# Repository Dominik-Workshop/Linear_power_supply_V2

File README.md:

# DW3005T - Linear power supply 2

This is the second iteration of my linear power supply project [available on GitHub](https://github.com/Dominik-Workshop/Linear_power_supply), building upon the foundation of my original design. While the first version served as an excellent learning experience, the DW3005T aims to improve upon its predecessor with enhanced performance, better stability, and a more professional design.

## Used tools:
 &nbsp;&nbsp;&nbsp;&nbsp; &nbsp;&nbsp;&nbsp;&nbsp; 

### Project Goals:
- **30V 5A output**
- **Very small output resistance**
- **Precise voltage, current and power measurements**
- **Small output noise**
- **Digital controll** - rotary encoder

## Electronics
### PCBs:
- Power board

<div align="center">
  
</div>

&nbsp;

- Control board
> [!WARNING]  
> WORK IN PROGRESS

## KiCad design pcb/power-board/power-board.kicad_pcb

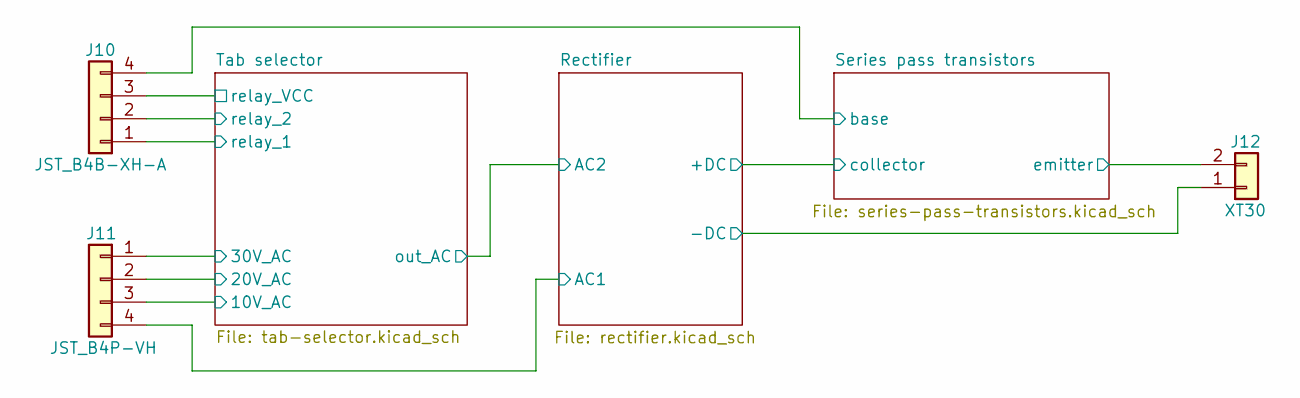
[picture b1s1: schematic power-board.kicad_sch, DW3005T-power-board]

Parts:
J10: JST_B4B-XH-A; JST_XH_B4B-XH-A_1x04_P2.50mm_Vertical
J11: JST_B4P-VH; JST_VH_B4P-VH_1x04_P3.96mm_Vertical
J12: XT30; AMASS_XT30U-F_1x02_P5.0mm_Vertical

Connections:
/Rectifier/-DC: J12.1; also elsewhere on the board
/Rectifier/AC1: J11.4; also elsewhere on the board
/Series pass transistors/base: J10.4; also elsewhere on the board
/Series pass transistors/emitter: J12.2; also elsewhere on the board
/Tab selector/10V_AC: J11.3; also elsewhere on the board
/Tab selector/20V_AC: J11.2; also elsewhere on the board
/Tab selector/30V_AC: J11.1; also elsewhere on the board
/Tab selector/relay_1: J10.1; also elsewhere on the board
/Tab selector/relay_2: J10.2; also elsewhere on the board
/Tab selector/relay_VCC: J10.3; also elsewhere on the board

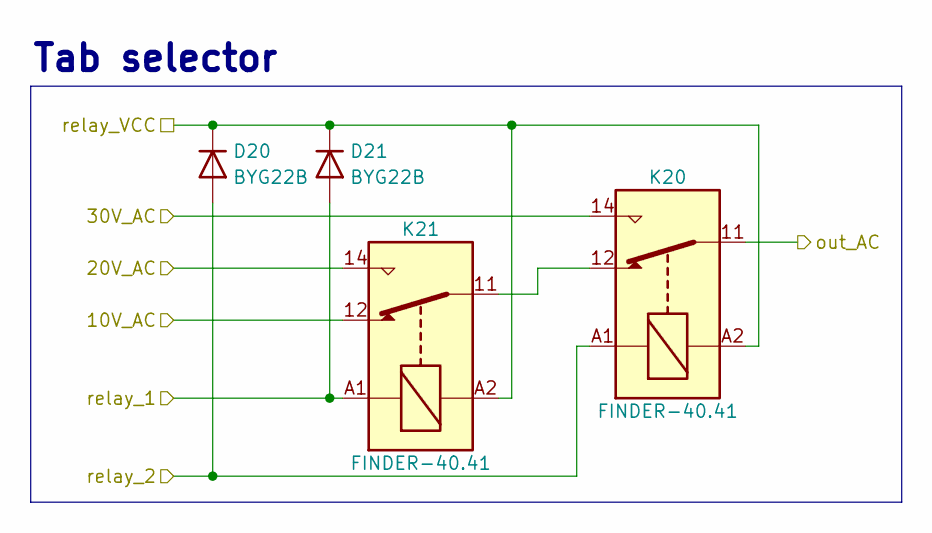
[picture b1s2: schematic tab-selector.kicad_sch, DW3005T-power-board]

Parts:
D20, D21: BYG22B; D_SMA; MPN BYG22B-E3/TR
K20, K21: FINDER-40.41; Relay_SPDT_Finder_36.11

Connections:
/Rectifier/AC2: K20.11; also elsewhere on the board
/Tab selector/10V_AC: K21.12; also elsewhere on the board
/Tab selector/20V_AC: K21.14; also elsewhere on the board
/Tab selector/30V_AC: K20.14; also elsewhere on the board
/Tab selector/relay_1: D21.2 (A), K21.A1; also elsewhere on the board
/Tab selector/relay_2: D20.2 (A), K20.A1; also elsewhere on the board
/Tab selector/relay_VCC: D20.1 (K), D21.1 (K), K20.A2, K21.A2; also elsewhere on the board
unnamed: K20.12, K21.11

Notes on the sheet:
Tab selector

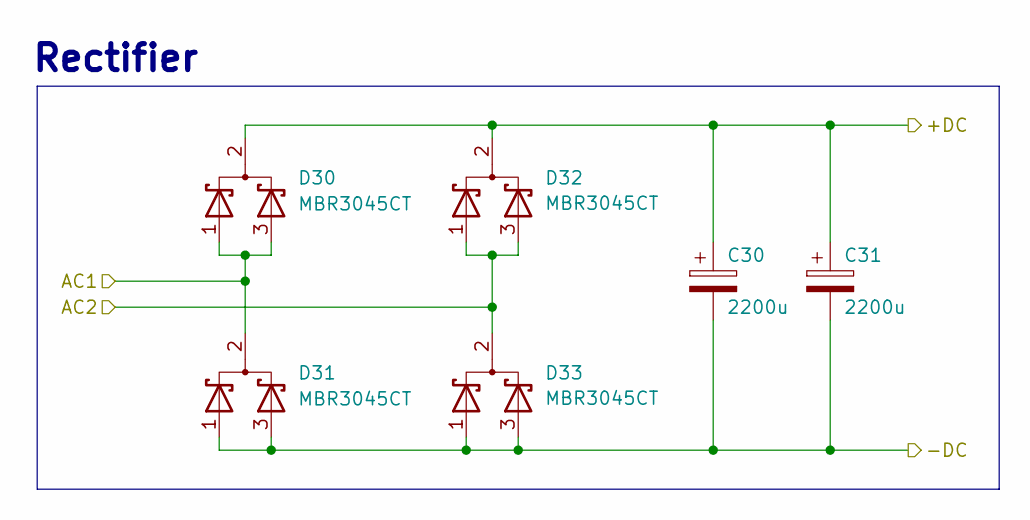
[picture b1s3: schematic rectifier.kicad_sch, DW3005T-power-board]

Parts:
C30, C31: 2200u; CP_Radial_D22.0mm_P10.00mm_SnapIn
D30, D31, D32, D33: MBR3045CT; TO-220-3_Horizontal_TabUp

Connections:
/Rectifier/+DC: C30.1, C31.1, D30.2 (A), D32.2 (A); also elsewhere on the board
/Rectifier/-DC: C30.2, C31.2, D31.1 (K), D31.3 (K), D33.1 (K), D33.3 (K); also elsewhere on the board
/Rectifier/AC1: D30.1 (K), D30.3 (K), D31.2 (A); also elsewhere on the board
/Rectifier/AC2: D32.1 (K), D32.3 (K), D33.2 (A); also elsewhere on the board

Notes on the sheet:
Rectifier

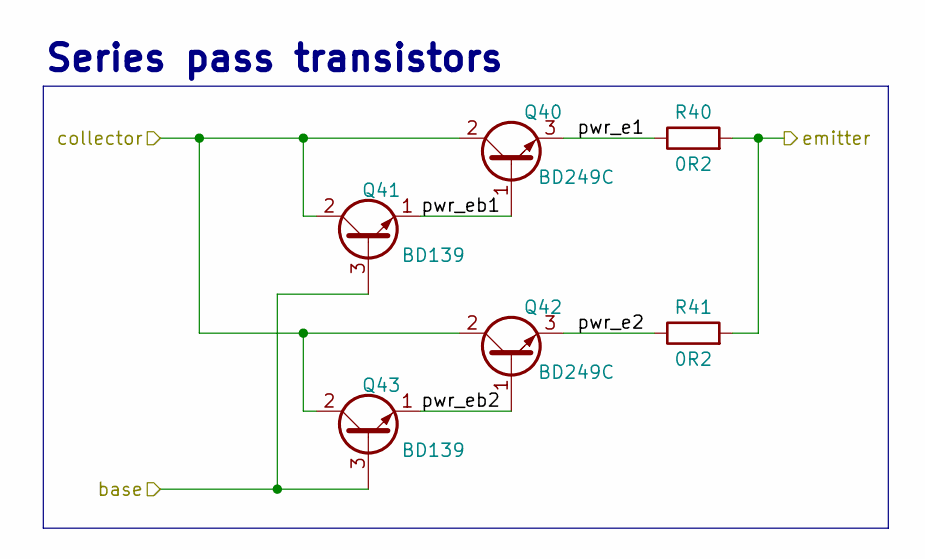
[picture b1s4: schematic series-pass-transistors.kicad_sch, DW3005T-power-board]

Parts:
Q40, Q42: BD249C; TO-247-3_Horizontal_TabUp
Q41, Q43: BD139; TO-126-3_Horizontal_TabUp
R40, R41: 0R2; R_Axial_DIN0414_L11.9mm_D4.5mm_P15.24mm_Horizontal

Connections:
/Rectifier/+DC: Q40.2 (C), Q41.2 (C), Q42.2 (C), Q43.2 (C); also elsewhere on the board
/Series pass transistors/base: Q41.3 (B), Q43.3 (B); also elsewhere on the board
/Series pass transistors/emitter: R40.2, R41.2; also elsewhere on the board
/Series pass transistors/pwr_e1: Q40.3 (E), R40.1
/Series pass transistors/pwr_e2: Q42.3 (E), R41.1
/Series pass transistors/pwr_eb1: Q40.1 (B), Q41.1 (E)
/Series pass transistors/pwr_eb2: Q42.1 (B), Q43.1 (E)

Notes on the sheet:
Series pass transistors

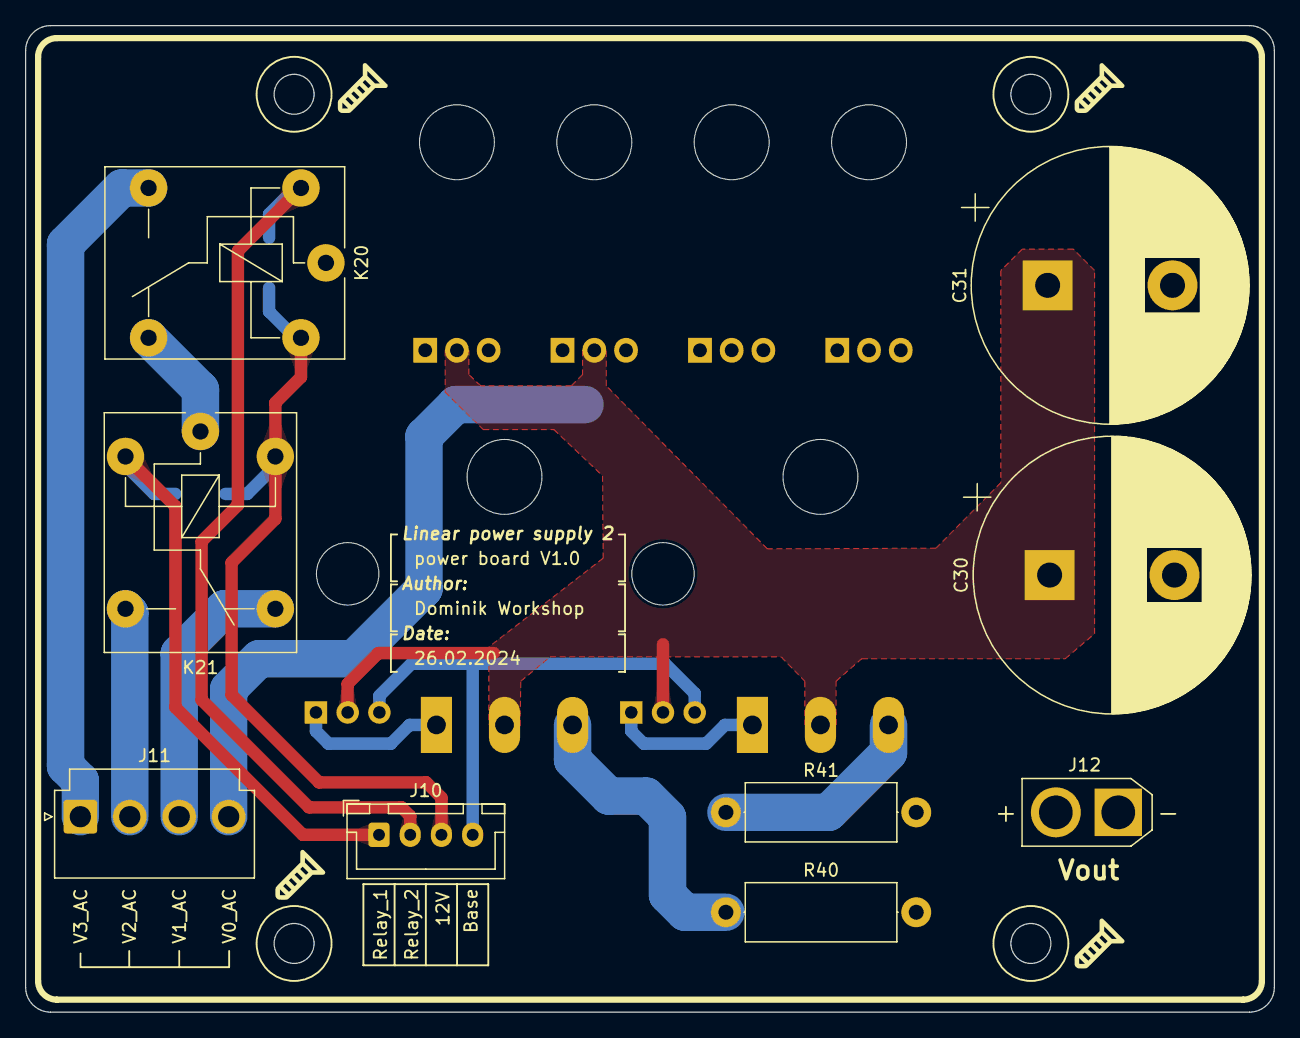
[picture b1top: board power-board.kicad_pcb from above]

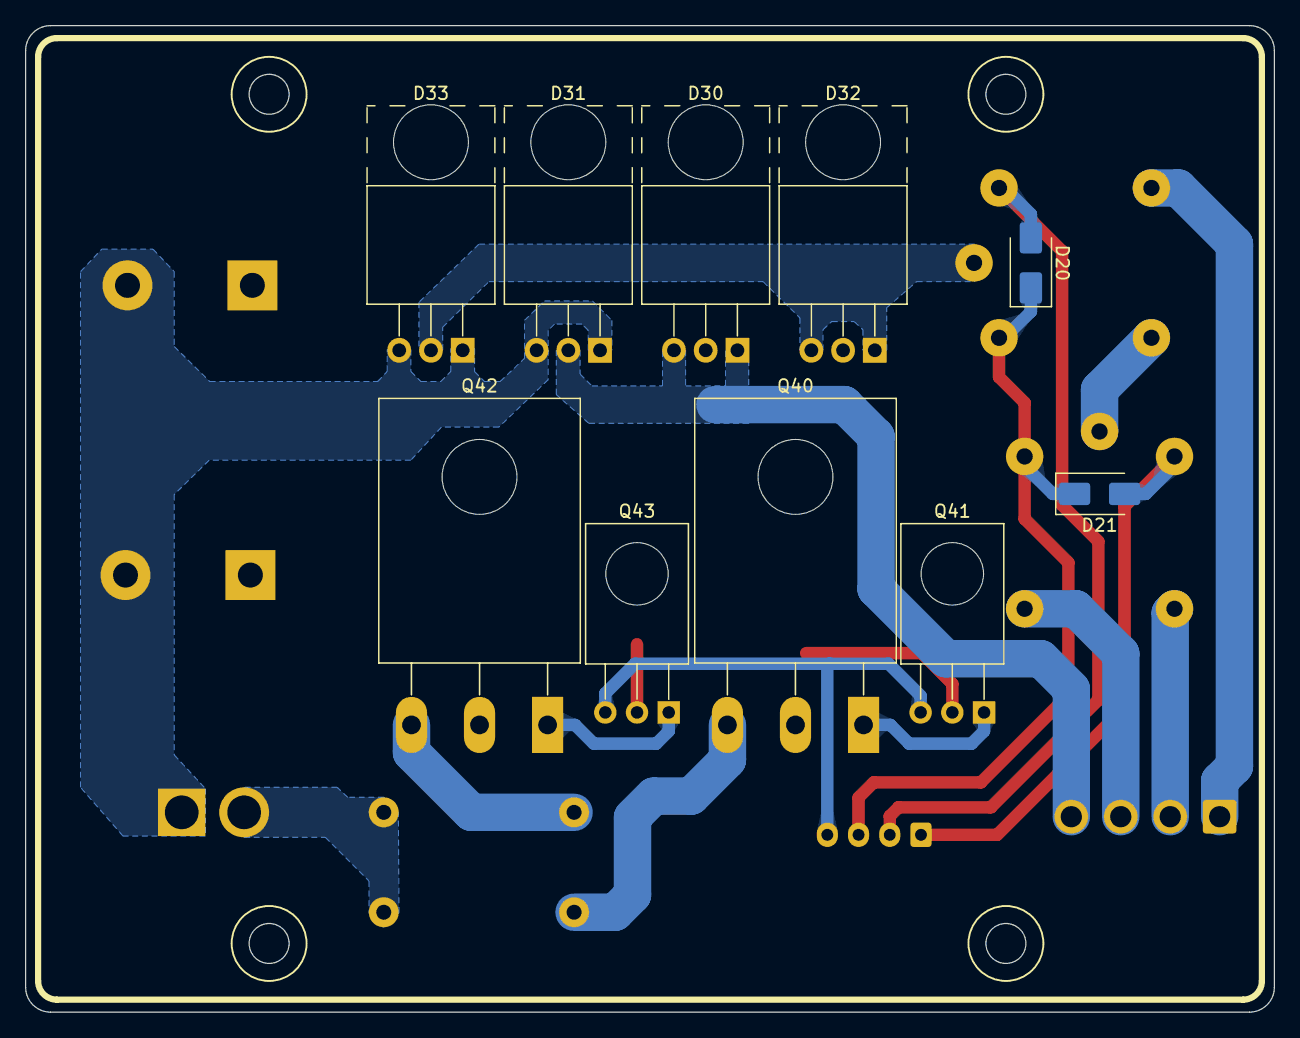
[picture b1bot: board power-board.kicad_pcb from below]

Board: 2 copper layers, 100.0 x 79.0 mm, 19 parts (10 on the bottom side), 17 nets.

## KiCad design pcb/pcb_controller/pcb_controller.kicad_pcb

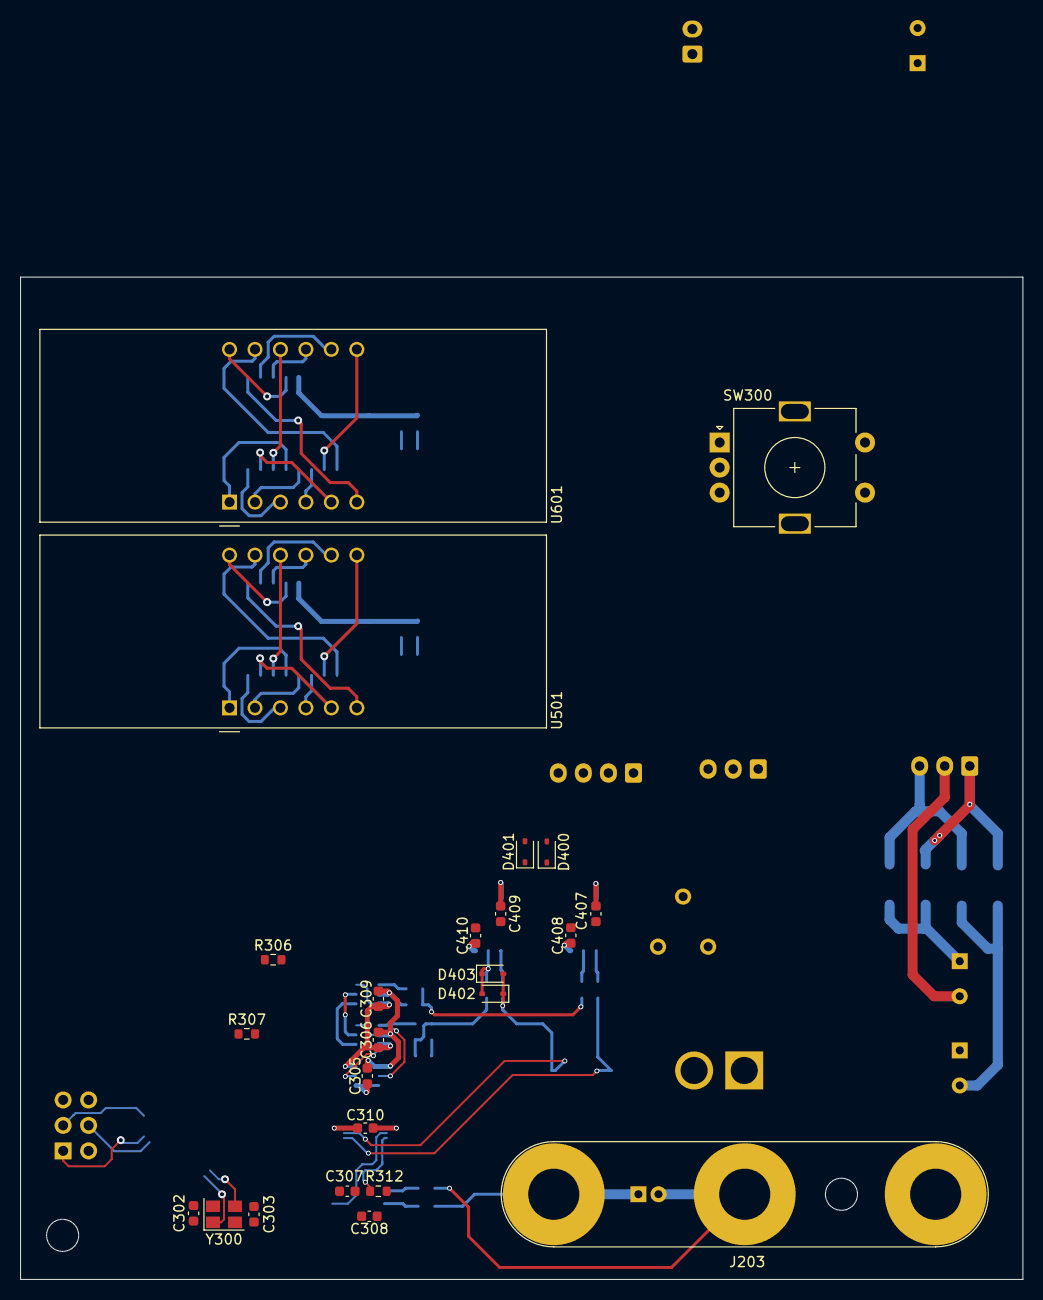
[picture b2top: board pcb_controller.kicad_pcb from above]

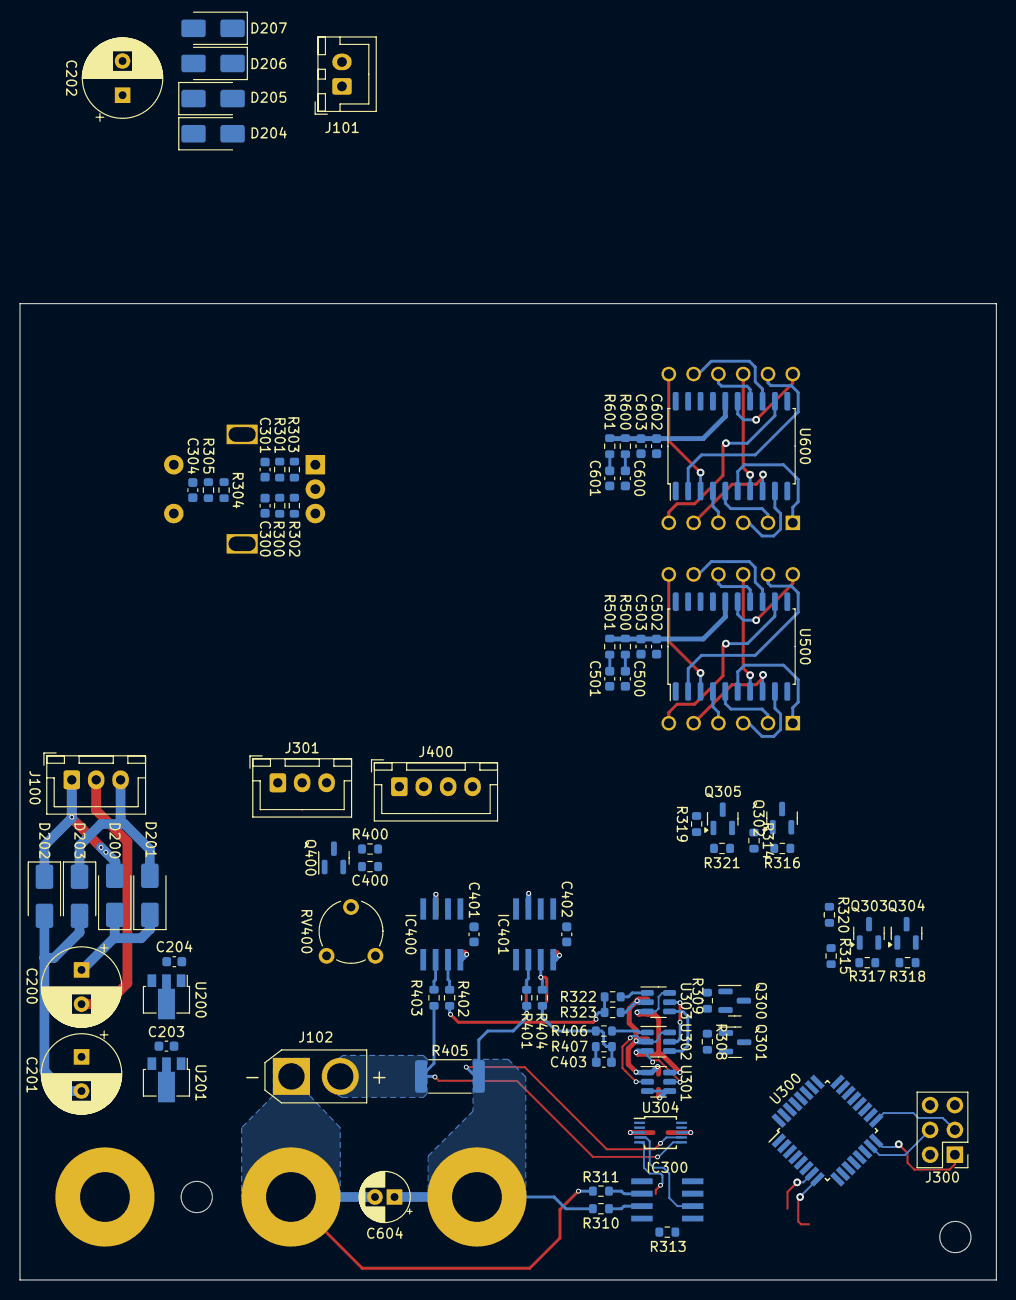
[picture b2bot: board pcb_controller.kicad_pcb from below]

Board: 2 copper layers, 100.0 x 100.0 mm, 112 parts (88 on the bottom side), 81 nets.

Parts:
C200, C201, C202: 1000u; CP_Radial_D8.0mm_P3.50mm
C203, C204, C300, C301, C304, C306, C307, C308, C309, C310, C407, C408, C409, C410, C502, C602: 100n; C_0603_1608Metric
C302, C303: 20p; C_0603_1608Metric
C305: 470n; C_0603_1608Metric
C400: 10u; R_0603_1608Metric
C401, C402: 22p; C_0603_1608Metric
C403: 1n; C_0603_1608Metric
C500, C501, C600, C601: 100p; C_0603_1608Metric
C503, C603: 10u; C_0603_1608Metric
C604: 10u; CP_Radial_D5.0mm_P2.00mm
D200, D201, D202, D203, D204, D205, D206, D207: B360; D_SMA
D400, D401, D402, D403: 1N4148WS; D_SOD-323
IC300, IC400, IC401: OPA277; SO08
J100, J301: JST_XH_B3B-XH; JST_XH_B3B-XH-A_1x03_P2.50mm_Vertical
J101: JST_XH_B2B-XH; JST_XH_B2B-XH-A_1x02_P2.50mm_Vertical
J102: XT30; AMASS_XT30U-M_1x02_P5.0mm_Vertical
J203: Banana conn; Banana_Jack_3Pin
J300: Goldpin_2x3; PinHeader_2x03_P2.54mm_Vertical
J400: JST_XH_B4B-XH; JST_XH_B4B-XH-A_1x04_P2.50mm_Vertical
Q300, Q301, Q303: 2N7002; SOT-23
Q302, Q305: CJ2306; SOT-23
Q304: BSS83P; SOT-23
Q400: S9015; SOT-23
R300, R301, R302, R303, R304, R305, R306, R307, R308, R309, R322, R323, R404: 4k7; R_0603_1608Metric
R310, R311: 100k; R_0603_1608Metric
R312, R313, R316, R317, R318, R320, R321, R401, R402, R500, R501, R600, R601: 10k; R_0603_1608Metric
R314, R315, R319, R400: 220R; R_0603_1608Metric
R403: 22k; R_0603_1608Metric
R405: 15m; R_2512_6332Metric
R406: 10k?; R_0603_1608Metric
R407: 100k?; R_0603_1608Metric
RV400: 4k7; Potentiometer_Piher_PT-6-V_Vertical
SW300: RotaryEncoder_Switch; RotaryEncoder_Alps_EC11E-Switch_Vertical_H20mm
U200: MC78L05; SOT-89-3
U201: MC79L05; SOT-89-3
U300: ATmega328P-A; TQFP-32_7x7mm_P0.8mm
U301: REF3240; SOT-23-6
U302, U303: MCP4725; SOT-23-6
U304: ADS1115IDGS; TSSOP-10_3x3mm_P0.5mm
U500, U600: TM1637; SOP-20_7.5x12.8mm_P1.27mm
U501, U601: CL5641BH; CA56-12SURKWA
Y300: 16MHz; Crystal_SMD_SeikoEpson_TSX3225-4Pin_3.2x2.5mm

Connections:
+4V: C306.2, C309.2, Q300.1 (G), Q301.1 (G), R308.1, R309.1, U301.5 (OUT_S), U301.6 (OUT_F), U302.3 (VDD), U303.3 (VDD), U303.6 (A0)
+5V: C204.2, C305.2, C307.2, C310.2, C400.1, C407.2, C409.1, C502.1, C503.1, C602.1, C603.1, IC300.7, IC400.7, IC401.7, J300.2, R302.2, R303.2, R304.2, R306.1, R307.1, R320.1, R400.2, R500.1, R501.1, R600.1, R601.1, RV400.1, U200.1 (OUT), U300.4 (VCC), U300.6 (VCC), U300.18 (AVCC), U301.3 (ENABLE), U301.4 (VIN), U304.8 (VDD), U500.16 (VDD), U600.16 (VDD)
+12V: C202.1, D204.1 (K), D205.1 (K), J400.3, Q304.2 (S), R318.1
-5V: C203.1, C308.1, C408.2, C410.2, IC300.4, IC400.4, IC401.4, U201.3 (VO)
/Linear regulator/+in_CC_amp: IC400.3, R402.2
/Linear regulator/+in_CV_amp: D402.2 (A), D403.1 (K), IC401.3, R404.2
/Linear regulator/-Vin: C403.1, C604.2, J102.1, J203.2, R311.1, R407.2
/Linear regulator/-in_CC_amp: C401.2, IC400.2, R403.2
/Linear regulator/-in_CV_amp: C402.2, IC401.2, R401.2
/Linear regulator/I_set: R322.2, R323.1, R402.1
/Linear regulator/U_set: R406.1, U302.1 (VOUT)
/Linear regulator/Vout_div: C403.2, R404.1, R406.2, R407.1
/Linear regulator/ccs_b: C400.2, Q400.2 (B), RV400.2
/Linear regulator/ccs_e: Q400.3 (E), R400.1
/Linear regulator/out_CC_amp: C401.1, D400.1 (K), IC400.6
/Linear regulator/out_CV_amp: C402.1, D401.1 (K), IC401.6
/Linear regulator/pwr_base: D400.2 (A), D401.2 (A), J400.4, Q400.1 (C)
/MCU/+in_s_amp: IC300.3, R310.2, R312.1
/MCU/-in_s_amp: IC300.2, R311.2, R313.1
/MCU/I_DAC_out: R322.1, U303.1 (VOUT)
/MCU/I_disp_CLK: C601.1, R601.2, U300.9 (PD5), U600.18 (CLK)
/MCU/I_disp_DIO: C600.1, R600.2, U300.2 (PD4), U600.17 (DIO)
/MCU/MISO: J300.1, U300.16 (PB4)
/MCU/MOSI: J300.4, U300.15 (PB3)
/MCU/RST: J300.5, U300.29 (~RESET/PC6)
/MCU/SCK: J300.3, U300.17 (PB5)
/MCU/SCL: Q300.3 (D), R306.2, U300.28 (PC5), U304.10 (SCL)
/MCU/SCL_4V: Q300.2 (S), R309.2, U302.5 (SCL), U303.5 (SCL)
/MCU/SDA: Q301.3 (D), R307.2, U300.27 (PC4), U304.9 (SDA)
/MCU/SDA_4V: Q301.2 (S), R308.2, U302.4 (SDA), U303.4 (SDA)
/MCU/U_disp_CLK: C501.1, R501.2, U300.11 (PD7), U500.18 (CLK)
/MCU/U_disp_DIO: C500.1, R500.2, U300.10 (PD6), U500.17 (DIO)
/MCU/Vout_meas: IC300.6, R313.2, U304.4 (AIN0)
/MCU/XTAL1: C303.1, U300.7 (XTAL1/PB6), Y300.3
/MCU/XTAL2: C302.1, U300.8 (XTAL2/PB7), Y300.1
/MCU/_e_A: R301.2, R303.1, SW300.A
/MCU/_e_B: R300.2, R302.1, SW300.B
/MCU/_e_bt: R304.1, R305.1, SW300.S1
/MCU/enc_A: C301.1, R301.1
/MCU/enc_B: C300.1, R300.1
/MCU/enc_button: C304.1, R305.2
/MCU/fan_tacho: J301.3, R320.2
/MCU/fan_v+: J301.2, Q304.3 (D)
/MCU/fpwm_g: Q303.3 (D), Q304.1 (G), R318.2
/MCU/fpwm_r: Q303.1 (G), R315.1, R317.1
/MCU/r1g_r: Q302.1 (G), R314.1, R316.1
/MCU/r2g_r: Q305.1 (G), R319.1, R321.1
/MCU/relay1: J400.1, Q302.3 (D)
/MCU/relay2: J400.2, Q305.3 (D)
/Power/12VAC1: D204.2 (A), D206.1 (K), J101.2
/Power/12VAC2: D205.2 (A), D207.1 (K), J101.1
/Power/+7VAC: D201.2 (A), D203.1 (K), J100.3
/Power/+9V_unreg: C200.1, D200.1 (K), D201.1 (K), U200.3 (IN)
/Power/-7VAC: D200.2 (A), D202.1 (K), J100.1
/Power/-9V_unreg: C201.2, D202.2 (A), D203.2 (A), U201.2 (VI)
GND: C200.2, C201.1, C202.2, C203.2, C204.1, C300.2, C301.2, C302.2, C303.2, C304.2, C305.1, C306.1, C307.1, C308.2, C309.1, C310.1, C407.1, C408.1, C409.2, C410.1, C500.2, C501.2, C502.2, C503.2, C600.2, C601.2, C602.2, C603.2, C604.1, D206.2 (A), D207.2 (A), D402.1 (K), D403.2 (A), J100.2, J203.1, J300.6, J301.1, Q302.2 (S), Q303.2 (S), Q305.2 (S), R310.1, R312.2, R316.2, R317.2, R321.2, R323.2, R401.1, R405.2, RV400.3, SW300.C, SW300.S2, U200.2 (GND), U201.1 (GND), U300.3 (GND), U300.5 (GND), U300.21 (GND), U301.1 (GNDF), U301.2 (GNDS), U302.2 (VSS), U302.6 (A0), U303.2 (VSS), U304.1 (ADDR), U304.3 (GND), U304.5 (AIN1), U304.7 (AIN3), U500.1 (GND), U600.1 (GND), Y300.2, Y300.4
I_meas: J102.2, R403.1, R405.1, U304.6 (AIN2)
unnamed: U500.15 (GRID1), U501.12 (CA1)
unnamed: U500.14 (GRID2), U501.9 (CA2)
unnamed: U500.13 (GRID3), U501.8 (CA3)
unnamed: U500.12 (GRID4), U501.6 (CA4)
unnamed: U500.2 (SEG1/KS1), U501.11 (a)
unnamed: U500.3 (SEG2/KS2), U501.7 (b)
unnamed: U500.4 (SEG3/KS3), U501.4 (c)
unnamed: U500.5 (SEG4/KS4), U501.2 (d)
unnamed: U500.6 (SEG5/KS5), U501.1 (e)
unnamed: U500.7 (SEG6/KS6), U501.10 (f)
unnamed: U500.8 (SEG7/KS7), U501.5 (g)
unnamed: U500.9 (SEG8/KS8), U501.3 (DPX)
unnamed: U600.15 (GRID1), U601.12 (CA1)
unnamed: U600.14 (GRID2), U601.9 (CA2)
unnamed: U600.13 (GRID3), U601.8 (CA3)
unnamed: U600.12 (GRID4), U601.6 (CA4)
unnamed: U600.2 (SEG1/KS1), U601.11 (a)
unnamed: U600.3 (SEG2/KS2), U601.7 (b)
unnamed: U600.4 (SEG3/KS3), U601.4 (c)
unnamed: U600.5 (SEG4/KS4), U601.2 (d)
unnamed: U600.6 (SEG5/KS5), U601.1 (e)
unnamed: U600.7 (SEG6/KS6), U601.10 (f)
unnamed: U600.8 (SEG7/KS7), U601.5 (g)
unnamed: U600.9 (SEG8/KS8), U601.3 (DPX)

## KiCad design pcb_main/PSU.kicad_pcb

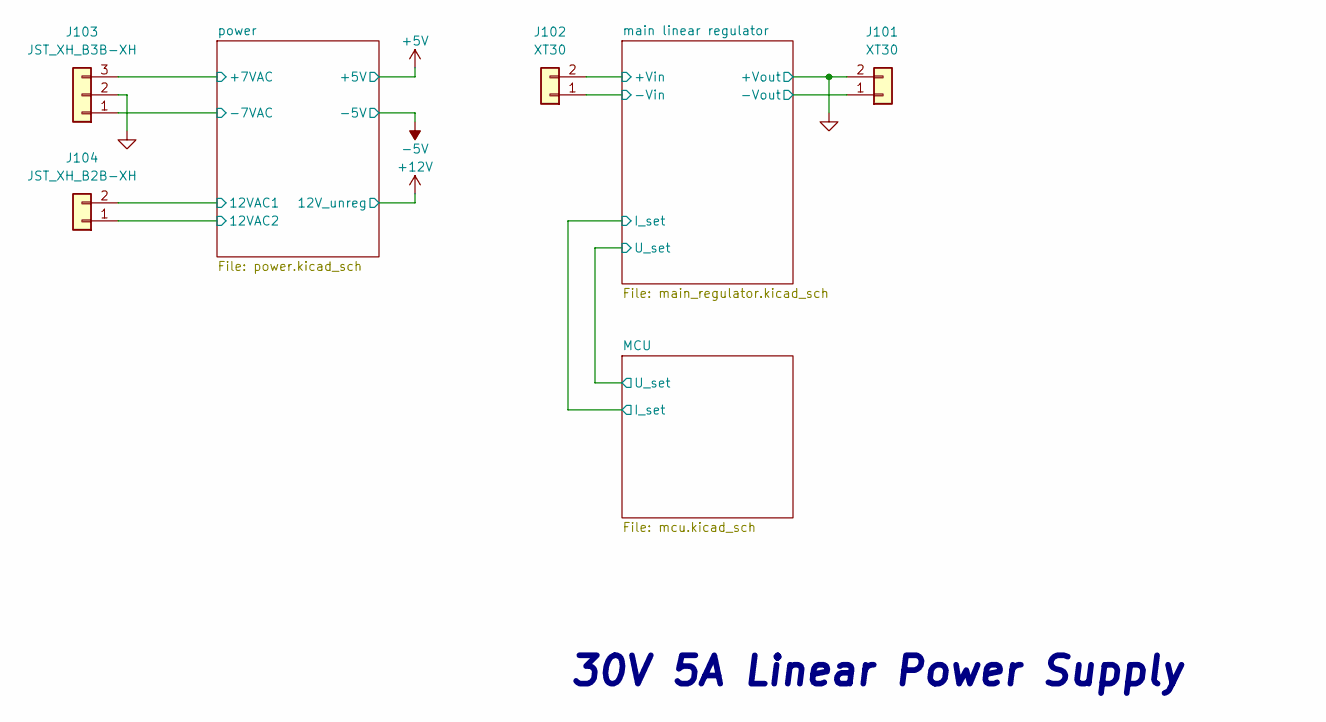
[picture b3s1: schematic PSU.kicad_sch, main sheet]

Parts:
J101, J102: XT30; AMASS_XT30U-M_1x02_P5.0mm_Vertical
J103: JST_XH_B3B-XH; JST_XH_B3B-XH-A_1x03_P2.50mm_Vertical
J104: JST_XH_B2B-XH; JST_XH_B2B-XH-A_1x02_P2.50mm_Vertical

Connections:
/main linear regulator/+Vin: J102.2; also elsewhere on the board
/main linear regulator/-Vin: J101.1, J102.1; also elsewhere on the board
/power/12VAC1: J104.2; also elsewhere on the board
/power/12VAC2: J104.1; also elsewhere on the board
/power/+7VAC: J103.3; also elsewhere on the board
/power/-7VAC: J103.1; also elsewhere on the board
GND: J101.2, J103.2; also elsewhere on the board

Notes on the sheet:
30V 5A Linear Power Supply

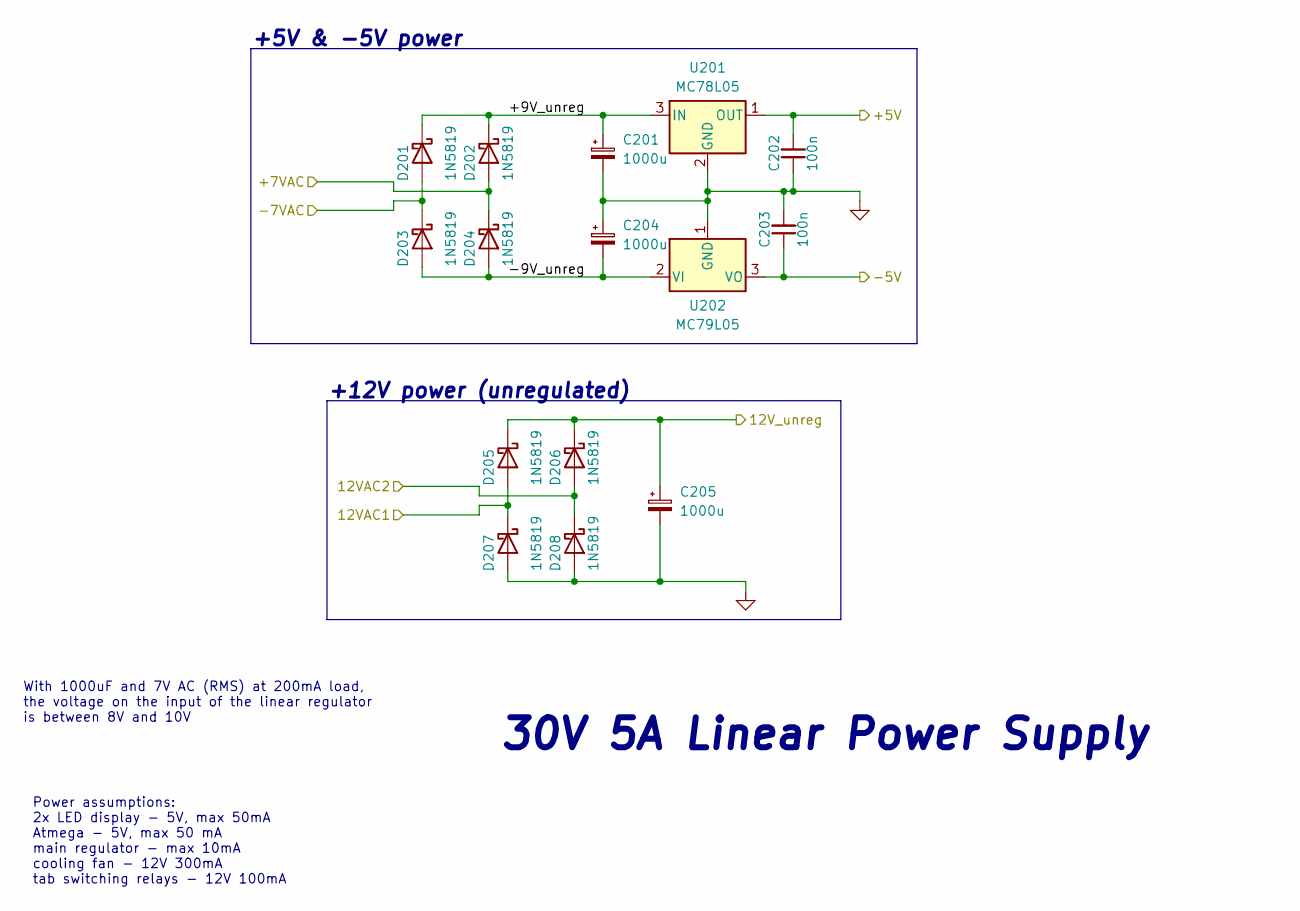
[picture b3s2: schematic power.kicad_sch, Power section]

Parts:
C201, C204, C205: 1000u; CP_Radial_D8.0mm_P3.50mm
C202, C203: 100n; C_0603_1608Metric
D201, D202, D203, D204, D205, D206, D207, D208: 1N5819; D_DO-41_SOD81_P10.16mm_Horizontal
U201: MC78L05; SOT-89-3
U202: MC79L05; SOT-89-3

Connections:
+5V: C202.2, U201.1 (OUT); also elsewhere on the board
+12V: C205.1, D205.1 (K), D206.1 (K)
-5V: C203.1, U202.3 (VO); also elsewhere on the board
/power/12VAC1: D205.2 (A), D207.1 (K); also elsewhere on the board
/power/12VAC2: D206.2 (A), D208.1 (K); also elsewhere on the board
/power/+7VAC: D202.2 (A), D204.1 (K); also elsewhere on the board
/power/+9V_unreg: C201.1, D201.1 (K), D202.1 (K), U201.3 (IN)
/power/-7VAC: D201.2 (A), D203.1 (K); also elsewhere on the board
/power/-9V_unreg: C204.2, D203.2 (A), D204.2 (A), U202.2 (VI)
GND: C201.2, C202.1, C203.2, C204.1, C205.2, D207.2 (A), D208.2 (A), U201.2 (GND), U202.1 (GND); also elsewhere on the board

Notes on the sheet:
30V 5A Linear Power Supply
Power assumptions: 2x LED display - 5V, max 50mA Atmega - 5V, max 50 mA main regulator - max 10mA cooling fan - 12V 300mA tab switching relays - 12V 100mA
+5V & -5V power
+12V power (unregulated)
With 1000uF and 7V AC (RMS) at 200mA load, the voltage on the input of the linear regulator is between 8V and 10V

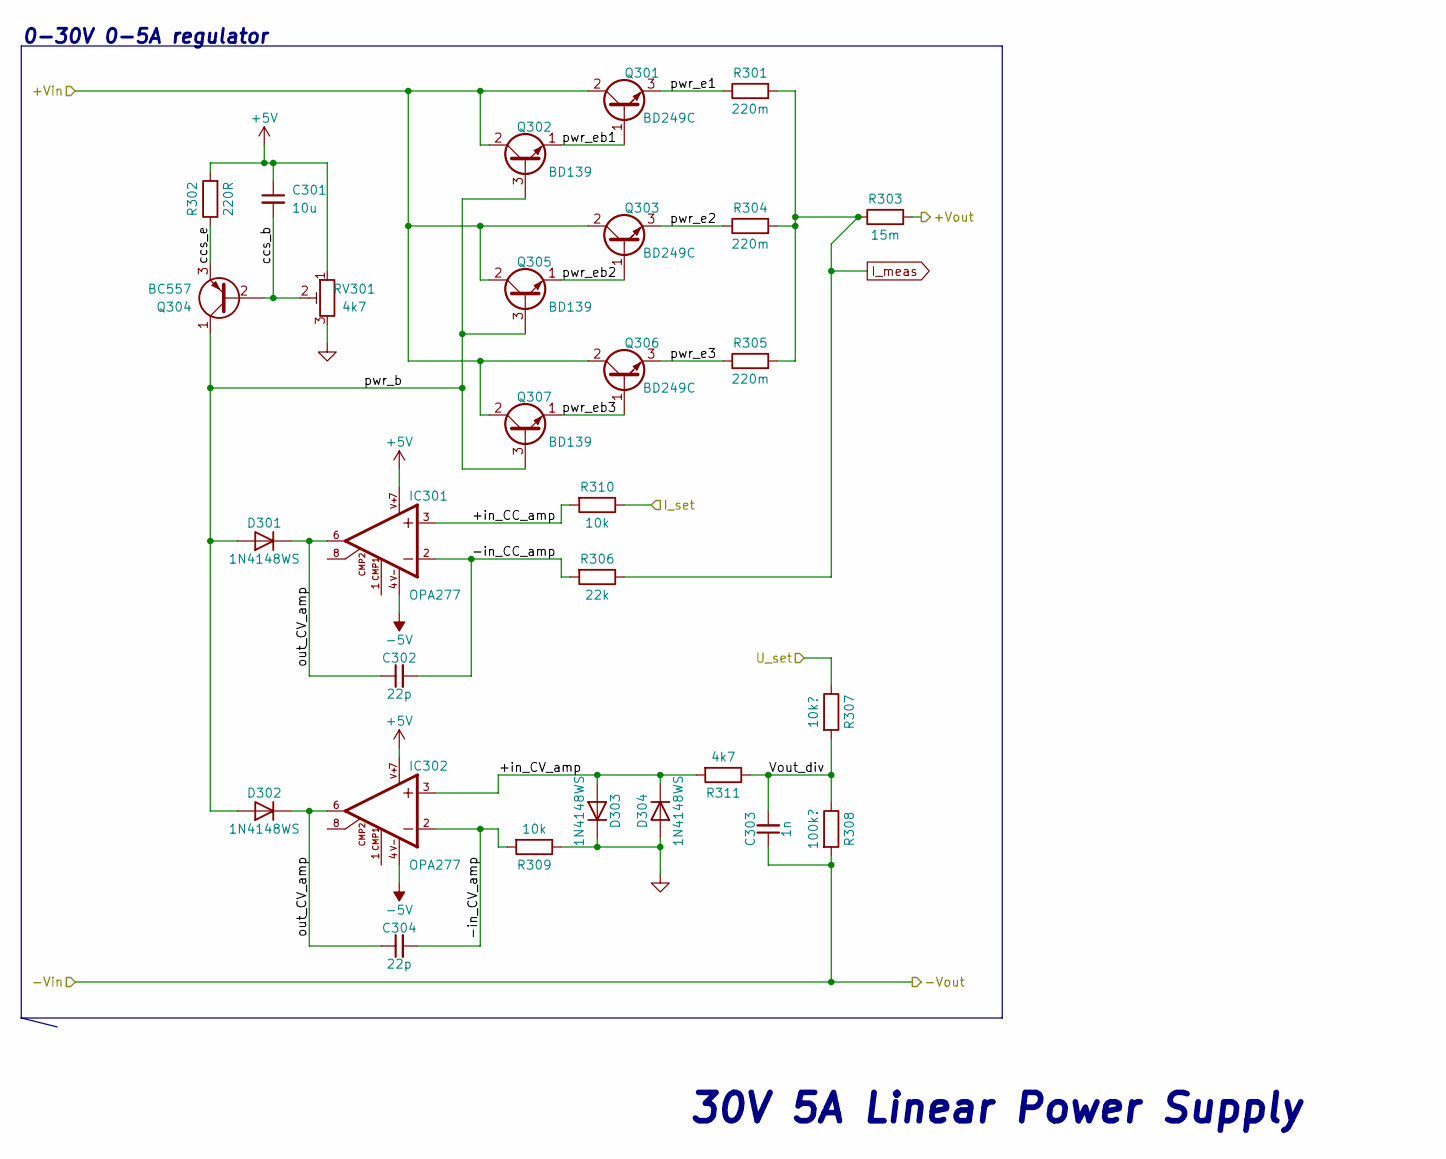
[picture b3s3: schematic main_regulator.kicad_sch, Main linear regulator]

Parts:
C301: 10u; R_0603_1608Metric
C302, C304: 22p; C_0603_1608Metric
C303: 1n; C_0603_1608Metric
D301, D302, D303, D304: 1N4148WS; D_SOD-323
IC301, IC302: OPA277; SO08
Q301, Q303, Q306: BD249C; TO-247-3_Horizontal_TabUp
Q302, Q305, Q307: BD139; TO-126-3_Horizontal_TabUp
Q304: BC557; SOT-23
R301, R304, R305: 220m; R_Axial_DIN0414_L11.9mm_D4.5mm_P15.24mm_Horizontal
R302: 220R; R_0603_1608Metric
R303: 15m; R_2512_6332Metric; Tolerance 1%; Power rating 3W; MPN LRP12FTDRR015
R306: 22k; R_0603_1608Metric
R307: 10k?; R_0603_1608Metric
R308: 100k?; R_0603_1608Metric
R309, R310: 10k; R_0603_1608Metric
R311: 4k7; R_0603_1608Metric
RV301: 4k7; Potentiometer_Piher_PT-6-V_Vertical

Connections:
+5V: C301.1, IC301.7, IC302.7, R302.2, RV301.1; also elsewhere on the board
-5V: IC301.4, IC302.4; also elsewhere on the board
/MCU/I_set: R310.1; also elsewhere on the board
/MCU/U_set: R307.1; also elsewhere on the board
/main linear regulator/+Vin: Q301.2 (C), Q302.2 (C), Q303.2 (C), Q305.2 (C), Q306.2 (C), Q307.2 (C); also elsewhere on the board
/main linear regulator/+in_CC_amp: IC301.3, R310.2
/main linear regulator/+in_CV_amp: D303.2 (A), D304.1 (K), IC302.3, R311.2
/main linear regulator/-Vin: C303.1, R308.2; also elsewhere on the board
/main linear regulator/-in_CC_amp: C302.2, IC301.2, R306.2
/main linear regulator/-in_CV_amp: C304.2, IC302.2, R309.2
/main linear regulator/Vout_div: C303.2, R307.2, R308.1, R311.1
/main linear regulator/ccs_b: C301.2, Q304.2 (B), RV301.2
/main linear regulator/ccs_e: Q304.3 (E), R302.1
/main linear regulator/out_CV_amp: C302.1, C304.1, D301.1 (K), D302.1 (K), IC301.6, IC302.6
/main linear regulator/pwr_b: D301.2 (A), D302.2 (A), Q302.3 (B), Q304.1 (C), Q305.3 (B), Q307.3 (B)
/main linear regulator/pwr_e1: Q301.3 (E), R301.1
/main linear regulator/pwr_e2: Q303.3 (E), R304.1
/main linear regulator/pwr_e3: Q306.3 (E), R305.1
/main linear regulator/pwr_eb1: Q301.1 (B), Q302.1 (E)
/main linear regulator/pwr_eb2: Q303.1 (B), Q305.1 (E)
/main linear regulator/pwr_eb3: Q306.1 (B), Q307.1 (E)
GND: D303.1 (K), D304.2 (A), R303.2, R309.1, RV301.3; also elsewhere on the board
I_meas: R301.2, R303.1, R304.2, R305.2, R306.1; also elsewhere on the board

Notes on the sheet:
0-30V 0-5A regulator
30V 5A Linear Power Supply
